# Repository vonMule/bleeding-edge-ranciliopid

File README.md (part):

# PERFECT COFFEE PID 
(former bleeding edge ranciliopid)

## Do it yourself, open-source PID for your espresso machine  

Version 3.2.5

## Support / Contact
You can chat with us directly using our [discord server](https://discord.gg/VA5ZeacFdw).

## Videos

<details>
  <summary>Click for more videos!</summary>

| Description             |  Video |
:-----------------------------------------------:|:---------------------------------------------:
ESP32 Functions with full Softwarecontrol | 
Cleaning Mode | 
Waterlevel Sensor | 
Two cups of a double cappuccino with the new Steamfunction | 
</details>

&nbsp;

## Most important features compared to the rancilio-pid software:
1. New PID Controller "Multi-state PID with steadyPower (Bias)"
   - Target-Temperature for brewing and steaming (!) is automatically controlled by PID.
   - Auto-Tuning of all PID settings. No knowledge or special tunings required.
   - Distinct PID settings dependend on the current "state" of the machine. 
   - Most of the settings are either static or semi-automatically tuned, which does not require an PHD (German: Diplom) to understand.
   - Currently 5 states are implemented:
     - Coldstart (machine is cold)
     - Coldstart stabilisation (directly after coldstart)
     - Inner Zone (temperature near setPoint)
     - Outer Zone (temperature outside of "inner zone")
     - Brewing
     - Steaming (!)
   - steadyPower is introduced which compensates the constant temperature loss due to environment
   - steadyPowerOffset is introduced which compensates the increased temperature loss when the machine (brew head etc.) is still very cold.
   - PidController offers feature like I-value filtering, special handling of setPoint crossings and more (hard-coded)
   - PID Controller is now integral part of the software and not an external library.
1. FULL ESP32 (and of cause esp8266) support in bleeding-edge main-branch.
1. Support of three hardware modifications which matches you requirements and offers the best flexibility.
   - PidOnly: This is the most basic modifcations in which only the heater is controlled by the esp.
   - Standard: In this modifcations in addition to the heater, "brewing" is also controlled by the esp which enables pre-infusion (by cutting the "hardware-button switched" power to the valve and the pump on demand).
   - FullControl: (ESP32 only) All functionality is directly controlled by the esp. This allows full customization and implementation of any feature. Also all functionality can therefore remotely be activated/deactivated. The ESP32 can run 24/7 if required.
1. Freely choose if you want the software to use WIFI, BLYNK and/or MQTT. Everythink can be enabled/disabled and still have a flawlessly working PID controller.
1. Additionally if you want to to depend on a remotely running service (eg. blynk server on raspi), you can activate a MQTT-Server on the arduino itself!
1. By using the actionController you can freely configure the system to trigger custom ACTIONS (=functions) when a GPIO port is triggered (eg by a switch) or when commands are received over network (mqtt/blynk).
   - fully dynamic mapping of any(!) available analog/digital gpio port to trigger following custom ACTIONS:
     - BREWING   := start brewing
     - STEAMING  := automatically manages heat up machine for steaming
     - HOTWATER  := start pouring hotwater
     - HEATER    := activate heater (not yet)
     - PUMP      := activate pump (not yet)
     - VALVE     := activate Valve  (not yet)
     - CLEANING  := activate cleaning mode
     - SLEEPING  := activate sleeping mode
     - MENU      := activate menu
     - MENU_INC  := increase value shown in menu
     - MENU_DEC  := decrease value shown in menu
   - while also supporting the switch types: toggles (eg switches) and triggers (eg push buttons)
   - added MQTT support to control ACTIONS using topics ../actions/<ACTION> with supported payloads of 0|1|-1 (off|on|switch)
     Example: "custom/Küche.Rancilio2/actions/STEAMING"
   - added Blynk support to control ACTIONS using virtual pins
1. MultiToggle triggers any ACTION based on multiple simultaneous hardware-button states (eg. if hotwater+steaming button is pressed then start the action CLEANING). MultiToggle can trigger up to six ACTIONS just by using the three rancilio's hardware-switches and therefore reduces the need for external control (mqtt, blynk, resistor-circuit, ..).
1. GpioAction: When actions are activated, specific GPIOs can be triggered also. This can be used eg. to light up LEDs in Rancilio's custom modified hardware-switches.
1. "Brew Profiles" can be used to easily set optimum brew settings for different beans.
1. Scale support to optionally brew by weight (in addition to by time).
1. Offline Modus is fixed and enhanced. If userConfig.h's FORCE_OFFLINE is enabled, then PID fully is working without networking. Ideal in situations when there is no connectivity or you dont want to rely on it.
1. Huge performance tunings and improvements under the hood which stabilizes the system (eg in situations of bad WIFI, hardware issues,..).
1. MQTT support to integrate machine in smart-home solutions and to easier extract details for graphing/alerting.
1. ACTION "SLEEPING" can be used to shutdown heater and turn the display off either after a period on user inactivity (default 120min) or by user request. Any user activity (controlActions, Hardware-Buttons, MQTT Actions, brew Detection,..) will wake up the maschine.
1. Added RemoteDebug over telnet so that we dont need USB to debug/tune pid anymore (https://github.com/JoaoLopesF/RemoteDebug). While using OTA updates you can remotely debug and update the software!
1. "Brew Ready" Detection implemented, which detects when the temperature has stabilized at setPoint. It can send an
   MQTT event or have hardware pin 15 triggered (which can be used to turn a LED on).
1. All heater power relevant settings are now set and given in percent (and not absolute output) and therefore better to understand
1. Support for customizable item collections to beautify display output (thanks to helge!)
1. Safetly toogle added to shutdown heater on sensor malfunction (TEMPSENSORRECOVERY)
1. Many useful functions to be used internally getAverageTemperature(), pastTemperatureChange() + updateTemperatureHistory())

## ATTENTION:
- This software is tested thoroughly with the pid-only hardware solution on Silvia 5e, and with a permanently run full-hardware solution on an 10 year old Silvia. Also a 10 year old Gaggia Classic is tested successfully. I am grateful for any further feedback. 
- Please monitor our machine's temperature closely the first few run times. The muti-state pid controller should never lead to temperatures greater than 5 degress above setpoint!

## Sample data log
- You can use the mqtt interface to export live data for monitoring purposes as can be seen in this [Grafana Dashboard](https://snapshot.raintank.io/dashboard/snapshot/lYe7XigrehSfVsvAWYifEwd2d5hNC0dl).

## Instructions on how to migrate from official rancilio to bleeding-edge
Installation is as explained on http://rancilio-pid.de/ but with following adapations:
1. Make screenshots of the official "Blynk App Dashboard" so that you can revert anytime.
1. Copy file userConfig.h.SAMPLE to userConfig.h and edit this file accordingly.
   - I propose to set MQTT_ENABLE=2 instead of blynk. But it is up to you.
     ```
     #define MQTT_ENABLE 2
     ```
1. Copy contents of folder ranciliopid\arduino-libs to your arduino sketchbook location (normally C:\Users\YOUR_NAME\Documents\Arduino)
   - Important: Open arduino IDE and configure the setting Tools->"lwip Variant" -> "1.4 High Bandwidth"
1. Flash and enjoy your espresso.
1. No tuning should be required normally. If you want/need to then use the method described below.

## Instructions on how to update to the latest version of bleeding-edge
1. Just overwrite all existing files with a newly released version.
2. Open your userConfig.h file, which had not been overwritten in previous step, and manually check (line by line!) that all updates to the new file userConfig.h.SAMPLE are reflected in your own userConfig.h. 
3. Compile, upload and enjoy!

## Remote Control APIs
- MQTT
  - Instructions can be found at https://github.com/medlor/bleeding-edge-ranciliopid/wiki/MQTT-Setup
- Blynk
  - Instructions can be found at https://github.com/medlor/bleeding-edge-ranciliopid/wiki/Blynk-Setup

## Tunings instructions
- Instructions can be found at https://github.com/medlor/bleeding-edge-ranciliopid/wiki/PID-Tuning

## Debugging Howto
- Instructions can be found at https://github.com/medlor/bleeding-edge-ranciliopid/wiki/Debugging-Howto

## How to use a simple LED as brewReady signal
- Instructions can be found at https://github.com/medlor/bleeding-edge-ranciliopid/wiki/How-to-use-a-simple-LED-as-brewReady-signal

## Instructions on how to create new icon collections
- Instructions can be found at https://github.com/medlor/bleeding-edge-ranciliopid/wiki/Instructions-on-how-to-create-new-icon-collections

## Changelog
- 3.2.5:
  - Feature: Add local(!) MQTT Broker support on ESP32. Finally you can have MQTT without an external running broker. Many thanks to bviecelli!
  - Fix: Upgrade to Expressif v6.5.0
  - Some bugfixes on the new broker integration.
- 3.2.4:
  - Many more refactorings by aschoelzhorn. Thanks again!
    - Seperated wifi, temperature and other code to dedicated files. 
    - Introduces rancilio-enums.h file and replaced some defines with enum classes.
    - Reorganized OTA (init and handle), OTA code still in "rancilio-pid.ino" because of timer stuff.
    - Separated declaration and implementation in some header/code files.
  - Part cleanup of includes.
  - Some bugfixes and refactorings by Tobias.
- 3.2.3:
  - Feature: On OTA Update show special logo and progress. Thanks aschoelzhorn!
  - Feature: Enable bigger status icons when ENABLE_BIG_STATUS_ICONS is set to 1 (default 0). Many thanks aschoelzhorn!
  - Refactor: Code refactorings. Many thanks aschoelzhorn!
  - Fix: Wifi stability improvements.
    - Disable WiFi Power Safe.
    - Reduce WiFi retry wait times.
    - WiFi instability by adding housekeeping times.
  - Changed minimum retry timer when mqtt/blynk disconnects happen from 160s to 60s.
  - Fix: Changing MQTT settings while machine being offline is being honored again.
  - Fix: Blynk working again with latest version.
  - Added Blynk state caching.
  - Fix: Some "include" issues when arduinoIDE is used. Thanks Helge!
  - Fix: Support for Expressif v5.3.
  - Performance improvements. 
  - Removed legacy grafana.
- 3.2.2:
  - Refactor: Moved blynk code into own files. Thanks aschoelzhorn!
  - Refactor: Add a temperature sensor mock. Thanks aschoelzhorn!
  - Refactor: Replace state magic numbers with meaningful names. Thanks aschoelzhorn!
  - Fix: Schematic_bleeding_edge_full_control_pcb_layout_v0.7.png, was wrong at one place.
- 3.2.1:
  - Feature: Add support for SH1106 in SPI mode. Thanks piontec!
  - Feature: Add support for custom display pins (see DISPLAY_I2C_SCL, DISPLAY_I2C_SDA). Thanks piontec!
  - Feature: Distinguish triggertype for 3way-valve and pump. Thanks piontec!
  - userConfig.h Changes:
    - Added VALVE_TRIGGERTYPE, PUMP_TRIGGERTYPE (default HIGH. Previously called TRIGGERTYPE).
    - RENAMED pinRelayVentil to pinRelayValve.
    - RENAMED pinRelayPumpe to pinRelayPump.
    - Added DISPLAY_I2C_SCL, DISPLAY_I2C_SDA (default 255).
  - Fix: SSD1306 support should also work again. Thanks piontec!
  - Added IoTMQTTPanel-perfect_coffee_pid_v3.2.0_v1.json to support the "new" scale settings.
  - Fix: Changed BREWTIME_END_DETECTION to type "bool" to improve handling of improper configuration.
  - Upgrade ZACWire to v2.0.0. Thanks Adrian/lebuni.
  - Refactored GpioCheck accordingly.
  - Updated ESP boardmanager and library dependencies to latest official version:
    - Platformio:
      - esp32: Upgrade espressif32 from v3 to v5
      - FastLED to v3.5.0
      - esp8266: Upgrade espressif8266 from v2 to v4
      - esp8266: Update to latest uMQTTBroker
    - ArduinoIDE:
      - Upgrade Boardmanager from 
        - ESP32:v1.0.6 to v2.0.4 
        - ESP8266:v2.7.4 to 3.0.2
      - Important: Update all manually installed libs like RemoteDebug and ZACWire (see Wiki)!
- 3.2.0:
  - NEW FEATURE (ESP32 & ONLYPID=0): Add *SCALE* functionality for brewing based on a PR by [Hoondie](https://github.com/avolmensky) (Many thanks Hoondie!).
    - Rewrite of brew() function to supports stopping brewing by time or weight (see userConfig.h BREWTIME_END_DETECTION):    
    - Setup guide in [Wiki](https://github.com/medlor/bleeding-edge-ranciliopid/wiki/Scale-Setup)
      - 3D printer models:
        - [3D Scale Case made by Hoondie](https://www.thingiverse.com/thing:5226789) (Many thanks Hoondie!).
        - [PerfectCoffeePid Scale Case](https://github.com/medlor/bleeding-edge-ranciliopid/tree/master/3d-models/PerfectCoffeePid-Scale). 
    - Display shows actual weight while brewing and additionally brewStatistics/flowRate a couple of seconds after brew (all themes are supported).
    - Automatic tuning of target-weight offset to adapt to dipping effects after brew ends.
  - Refactoring und noticeable further features:
    - Implemented manual calibration feature:
      - Howto: 
        - Set ENABLE_CALIBRATION_MODE=1, start machine without any weight on the scale, 
          after around 20s put a known weight (which is set in SCALE_SENSOR_CALIBRATION_WEIGHT) on the scale.
          The LOG will show the calculated SCALE_SENSOR_CALIBRATION_FACTOR which has to be added to the userConfig.h .
    - Send brewStatistics to display, mqtt events and LOG: "Brew statistics: 37.36g in 29.78s (1.25g/s) with profile 1".
      - FlowRate also included in output.
      - Display shows brewStatistics after brew for a couple of seconds.
    - Use powerOff and powerUp to save energy and to reduce interrupt conflicts. HX711 is only enabled when brew is running. 
    - 3rd party library for the HX711_ADC by Olav Kallhovd (https://github.com/olkal/HX711_ADC) adapted to our needs (Many thanks Olav!):
      - [custom async implementation](https://github.com/medlor/HX711_ADC) while using ISR to ...
        - reduce processing delays
        - reduce competing interrupts between TSIC, display and scale
        - no TSIC errors!
    - Auto-tare weight (async; without delay) at start of brew.
    - After brew is finished weight is measured for an additional 2 seconds (to include drops after the pump has stopped).
    - If HX711 cannot be initialized on start of brew, fallback to time-based brewing.
    - New scale settings are now tied to "Profiles":
      - Set following settings in userConfig.h / MQTT / "CONTROLS_CONFIG" / Blynk (V64 := activeBrewTimeEndDetection , V65 := activeScaleSensorWeightSetPoint):
        - BREWTIME_END_DETECTIONX: if 0, stop by time else stop by weight 
        - SCALE_SENSOR_WEIGHT_SETPOINTX = weight when to stop brewing
    - Custom scaleConfigOverwrite.h
    - ArduinoIDE: Added library/HX711_ADC_fix which has to be manually copied to your arduino library path. (see wiki)
    - ArduinoIDE: Successfully compiles (in addition to Platformio).
  - ArduinoIDE: "library/RemoteDebug" minor compile fix.
  - ArduinoIDE: Add check to force esp32 board version 1.0.6.
  - brew() is only called at most every 1ms.
  - Fix: If you have an analog toggle configured for BREWING and dont turn it off before power-off, 
      then brewing will no longer automatically start on power-on.
  - userConfig.h Changes:
    - BREWTIMER_MODE renamed to BREWTIME_TIMER
    - Many new defines called SCALE_SENSOR_*
    - Added BREWTIME_END_DETECTIONX
    - Added SCALE_SENSOR_WEIGHT_SETPOINTX.
    - Added SCALE_SENSOR_CALIBRATION_WEIGHT, SCALE_SENSOR_CALIBRATION_FACTOR
    - Updated circuit-diagrams to add HX711.
- 3.1.1:
  - Fix: Coldstart working again.
- 3.1.0:
  - NEW FEATURE: Add support for up to 3 "*Profiles*", which can be used to quickly switch between different brew settings (eg. when different beans are used).
    - An individual profile comprises of following settings:
      - Brew Temperature / setPoint
      - Brew Time 
      - Preinfusion time and pause
      - Coldstart Temperature / startTemp
    - Profiles can be selected by any means, eg mqtt/blynk/menu/.. . The variable for this is "profile".
    - The selected profile is also shown on the display, see new setting ENABLE_PROFILE_STATUS.
    - ATTENTION: Following variable names has changed and therefore any mqtt dashboards and tools have to be adapted (eg IotMQTT/Grafana/nodered):
      - setPoint -> activeSetPoint
      - brewtime -> activeBrewTime
      - starttemp -> activeStartTemp
      - preinfusion -> activePreinfusion
      - preinfusionpause -> activePreinfusionPause
      - Hint: Changing the value of any of variables (eg using mqtt/blynk) will update the respective setting of the currently activated profile.
    - Blynk:
      - Added new virtual Pin V3 for "profile", which can be any number between 1 and 3.
      - Added [Blynk Showcase](https://github.com/medlor/bleeding-edge-ranciliopid/tree/master/blynk/blynk-showcase_v3.1.0.mp4).
  - NEW FEATURE: Initial support for MENU which can be used to control settings using the display-case with buttons:
    - Action "MENU" added.
    - Actions TEMP_INC and TEMP_DEC renamed to MENU_INC and MENU_DEC respectively.
    - Added new userConfig.h setting MENU_CONFIG which is used to configure menu settings.
    - Following menu operations are supported (can be extended on request):
      - SETPOINT, SETPOINTSTEAM, BREWTIME, PREINFUSION, PREINFUSION_PAUSE, PID_ON
  - NEW FEATURE: The calculation of the "total brew time" can be adjusted with the userConfig.h setting BREWTIMER_MODE.
     - 0: (default) brewtime-countdown is equal BREWTIMEX. 
     - 1: brewtime-countdown is BREWTIMEX + PREINFUSIONX + PREINFUSION_PAUSEX
  - userConfig.h Changes:
    - Added:
      - ENABLE_PROFILE_STATUS
      - Renamed SETPOINT to SETPOINT1
      - Renamed BREWTIME to SETPOINT1
      - Renamed PREINFUSION to PREINFUSION1
      - Renamed PREINFUSION_PAUSE to PREINFUSION_PAUSE1
      - TEMPSENSOR (default=2)
      - SETPOINT2, SETPOINT3
      - STARTTEMP2, STARTTEMP3
      - PREINFUSION2, PREINFUSION3
      - PREINFUSION_PAUSE2, PREINFUSION_PAUSE3
      - BREWTIMER_MODE
  - Support for Thermistor K-type with MAX6675 (Thanks to aschoelzhorn for the PR and TeraK, sailhobie for support).
    - TSIC3xx is still strongly recommended to use!
  - Updated IoTMQTT Dashboard [IoTMQTTPanel-perfect_coffee_pid_v3.1.0_v1.json](https://github.com/medlor/bleeding-edge-ranciliopid/tree/master/IoTMQTTPanel/IoTMQTTPanel-perfect_coffee_pid_v3.1.0_v1.json) to include Profile and Action support. [Showcase](https://github.com/medlor/bleeding-edge-ranciliopid/tree/master/IoTMQTTPanel/IoTMQTT-showcase_v3.1.0.mp4).
  - Refactor and fix eeprom stuff.
  - Refactor all variables from double to float.
  - Make blynk optional on compilation.
  - Removed burst feature.
  - Fixes:
    - Fix blynk "heater output" not being shown.
    - Fix float compare function.  
- 3.0.0:
  - Project is getting renamed to "Perfect Coffee PID".
  - Improve temperature readings to reduce undesireable actions of the PID controller:
    - Detect outliers near setpoint and fix them automatically.
    - Read temperature every 100ms (previous 1s) and save it to TemperatureHistory for later use.
    - Implement average calculations on all temperature functions to stabilize temp readings.
    - Temporary use custom ZACwire library, which offer:
      - bitwindow auto-tuning right from the start.
      - directMode to improve outlier detection and flapping temperature in seldom cases (esp32).
      - Important: You have to [manually install](https://github.com/medlor/bleeding-edge-ranciliopid/wiki/How-to-compile-on-Arduino-and--Platformio) library/ZACwire_for_TSic (only if you are using Arduino IDE).
  - Add full support for platformio, code cleanup and fix compile warnings.
    - Force espressif8266 to Version 2 (until external libs are adapted)
  - Arduino IDE: Remove some libaries which from now on have to be installed manually, see [Wiki](https://github.com/medlor/bleeding-edge-ranciliopid/wiki/How-to-compile-on-Arduino-Platformio).
  - Performance improvement: 
    - controlActions are now using interrupts with an optional debounce feature (instead of polling each gpio).
  - Update ESP32 schematic to reflect recommendation to use 5v (instead of 3.3v) for the TSIC.
  - Fix: 
    - DISPLAY_TEXT_STATE is working on exp8266.
    - controllerActions: Improve debouncing of analog(ADC) and digital buttons/switches.
    - Improve steaming cycle-times.
  - Remove support for DS19B20 temperature sensors.
  - Improvements in error logging.
  - UserConfig Changes:
    - Breaking Change:
      - renamed DISPLAY to DISPLAY_HARDWARE
    - Removed:
      - TEMPSENSOR
    - Added:
      - DEBOUNCE_ANALOG_GPIO / DEBOUNCE_DIGITAL_GPIO
    - Changes:
      - recommended defaults
- 2.8.0:
  - Feature: Add support to detect low water using a VL53L0X Time of Flight distance sensor. see [Howto](https://github.com/medlor/bleeding-edge-ranciliopid/wiki/Water-level-measurement-using-VL53L0X-(Time-of-Flight-distance-sensor))
  - Helge supplied a 3d printing model for rancilio silvia's water tank lid which can be used with the VL53L0X sensor. (thanks Helge!)
  - Update ZACWire to v1.3.2. (Thanks Adrian)
  - UserConfig change: 
    - Renamed DEBUG_FORCE_GPIO_CHECK to ENABLE_CALIBRATION_MODE.
  - Fix: Show general logo when MASCHINE_TYPE is set to unknown.
- 2.7.1:
  - Added PR for automatic cleaning mode (Thanks to urbantrout/Harald).
    - Adaptions:
      - New cleaning icon: ["washing hand"](https://thenounproject.com/matfine/collection/cleaning-icon/?i=2749704) by [Mat fine](https://thenounproject.com/matfine) from [the Noun Project](https://thenounproject.com/matfine/collection/cleaning-icon/?i=2749704) licensed under [CC BY 3.0](https://creativecommons.org/licenses/by/3.0/legalcode)
      - New Blynk VPins (read-only/pull) defined: see [Blynk-Setup](https://github.com/medlor/bleeding-edge-ranciliopid/wiki/Blynk-Setup)
      - New userConfig Settings: 
        - CLEANING_CYCLES, CLEANING_INTERVAL, CLEANING_PAUSE.
        - Set CLEANING_ENABLE_AUTOMATIC=1 to use automatic cleaning program instead of manual modus.
  - Feature: (Silvia5E): ENABLE_POWER_OFF_COUNTDOWN timer (in minutes) is available via mqtt("powerOffTimer")/blynk(V45).
  - Blynk is fully supporting actionController. Therefore any action can be called via blynk. (see [Blynk-Setup](https://github.com/medlor/bleeding-edge-ranciliopid/wiki/Blynk-Setup))
  - Added new icon-collection "static" which just shows a non-moving logo.
  - Added userConfig DISPLAY_TEXT_STATE which outputs few status information (Please wait, Ready, Turned off, Cleaning, ..) in the display (supported by all icon-collections).
    - Text is not displayed when screensaver is running.
  - Fix: Waking up after SLEEPING action re-enables cold-start autotuning.
  - Fix: Blynk sometimes crashes when controlActions are changed.
  - Fix: SLEEPING action will turn off display even if ENABLE_SCREEN_SAVER=0.
  - Fix: DISPLAY_TEXT_STATE is not shown during BREWING.
  - Update ZACwire-Library to v1.3.1. and 1.3.0 (beta). (Thanks again Adrian :-) )
- 2.7.0:
  - Feature: FULLY SUPPORT ESP32 with CPU pinning for improved performance.
    - Unfortuately there is no mqtt-server broker library available for ESP32. (MQTT_ENABLE must not be 2 or disabled on ESP32)
    - Display function is pinned to secondary cpu to further improve performance. No more tearing on screen refresh.
  - [ZACwire-Library](https://github.com/lebuni/ZACwire-Library) upgrade to stable release v1.3.0 which supports ESP32 and pinning to secondary cpu. Thanks Adrian!
  - Feature: "FULL CONTROL" hardware modification is fully supported (in addition to the previous "PidOnly" and "standard" modification)!
    - FullControl have all(!) functionality directly controlled by the esp (eg. without the need to manually switch any buttons).
    - Instead of having the hardware-switches control brew/hotwater/steaming and have the esp just "cut" the wire, the FullControl modification detects button presses directly and translates them to any custom functionality (using ControlActions, MultiToggle and optionally GpioActions). This allows maximum flexibility.
  - Feature: The "MultiToggle" feature triggers any ControlAction based on multiple simultaneous hardware-button states (eg. if hotwater+steaming button is pressed then start the action cleaning).
    - This allows to use a total of six ControlActions just by using the three rancilio's hardware-switches and reduces the need for external control (mqtt, blynk, resistor-circuit, ..).
    - New UserConfig variables: MULTI_TOGGLE_?_ACTION and MULTI_TOGGLE_?_GPIOS.
  - Feature: GpioAction: If actions are activated, specific GPIOs can be triggered also. This can be used eg. to light up LEDs in Rancilio's [custom modified hardware-switches](https://voir.pt/2017/12/30/rancilio-silvia-bezugsschalter-als-softwareschalter-umruesten/).
    - userConfig.h: ENABLE_GPIO_ACTION / pinBrewAction / pinHotwaterAction / pinSteamingAction
    - CLEANING action will turn on the brew/hotwater/steaming gpios to make this state easily visible even when no display is used.
    - During PowerOn GpioActions and HardwareLed are enabled for a couple of seconds.
  - Feature: Added new state "SLEEPING", which shutdowns heater and turns display off either after a period on user inactivity (default 120min) or by user request using the new ControlAction "SLEEPING". Any user activity  (controlActions, Hardware-Buttons, MQTT Actions, brew Detection,..) will wake up the maschine.
    - New userConfig setting: userConfig HEATER_INACTIVITY_TIMER (0 to disable)
  - Feature: (!OnlyPid|Full Control) Added a CLEANING mode which sets pre-infusion pause to 0seconds and disables auto-tuning for as long as mode is active. Use "CLEANING" ControlAction or activate steaming to restore normal operation.
  - Feature: You can now set INPUT/INPUT_PULLDOWN/INPUT_PULLUP in CONTROLS_CONFIG. 
  - Feature: (ENABLE_HARDWARE_LED=2) New settings ENABLE_HARDWARE_LED_RGB_ON/ENABLE_HARDWARE_LED_RGB_OFF to set specific colors.
  - Breaking changes:
    - CONTROLS_CONFIG format changes to support new INPUT/INPUT_PULLDOWN/INPUT_PULLUP settings.
  - CHANGE: (DISPLAY=1) HardwareLed is not turned on when screensaver is running and ENABLE_HARDWARE_LED_OFF_WHEN_SCREENSAVER=1 (even if brew_ready state is reached).
  - Fix: Setting setPointSteam via mqtt did not work but did overwrite aggoTv instead. You should update to this version when using mqtt.
  - Fix: No one-time heater flapping if maschine is waked up from sleep or pidOff.
  - Fix: HardwareLed is only turned on, when temperature > steam_ready_temp AND steaming action is active.
  - Fix: (DISPLAY=1) HardwareLed is not turned on when screensaver is running (even if brew_ready state is reached).
  - Fix: Minor fixes here and there.
  - PubSubClient updated to version 2.8.
  - Update userConfig.h.SAMPLE (Thanks Helge)
  - Fix typos (Thanks urbantrout)
  - (ESP32) Added two new [circuit-diagrams](https://github.com/medlor/bleeding-edge-ranciliopid/tree/master/circuit-diagrams) which show the complete wiring in "full-control" upgrade.
  - Added several 3d models to print:
    - display-case-with-buttons
    - dual-ssr-relay-case
    - pcb-case (eg. to be used for esp32 on a pcb)
  - New images here and there.
  - Quick documentation on how to setup ESP32 can be found in the [wiki](https://github.com/medlor/bleeding-edge-ranciliopid/wiki/ESP32-Setup).
  - Thanks to Tobias for his helpful blog posts at [https://voir.pt](https://voir.pt/2017/12/30/rancilio-silvia-bezugsschalter-als-softwareschalter-umruesten/)
- 2.6.1:
  - Feature: Hardware-Led in addition to simple LEDs also support WS2812b LED (stripes) (MANY THANKS P1Rebo for the PR)
- 2.6.0:
  - Merged PR by finnito which changed/extended: (MANY THANKS FINNITO)
    - Added support for ECM espresso machine including logo.
    - Added/Extended support for special functions (steam, hotwater, brew).
    - Added custom steam functionality.
    - Extended initial support to call special functions based on Pin A0 (analog levels) which can be used by eg. hardware buttons.
    - Added new state to state machine (6=steam).
  - Refactored/Extended finnito's code to integrate our new "actionController":
    - fully dynamic mapping of any(!) available analog/digital gpio port to custom functions, which are currently:
      - BREWING   := start brewing
      - STEAMING  := automatically manages heat up machine for steaming
      - HOTWATER  := start pouring hotwater
      - HEATER    := activate heater (not yet)
      - PUMP      := activate pump (not yet)
      - VALVE     := activate Valve  (not yet)
      - CLEANING  := activate cleaning mode (not yet)
      - TEMP_INC  := increase setPoint (not yet)
      - TEMP_DEC  := decrease setPoint (not yet)
    - while also supporting the switch types: toggles (eg switches) and triggers (eg push buttons)
    - added MQTT Support to control actions using topics ../actions/<ACTION> with supported payloads of 0|1|-1 (off|on|switch)
      Example: "custom/Küche.Rancilio2/actions/STEAMING"
  - Feature: Set userConfig.h ROTATE_DISPLAY to rotate display 180 degree.
  - Feature: BrewReadyLed (now called HardwareLed) configured with ENABLE_HARDWARE_LED also lights up when temperature>steamTemp or >STEAM_READY_TEMP.
  - Feature: OnlyPid=0: Disable pre-infusion and pause if userConfig settings are set to 0.
  - Feature: OnlyPid=1: BrewDetection can also be triggered by hardware using actionControl "BREWING".
  - Feature: New userConfig setting SETPOINT_STEAM is also setable via [mqtt](https://github.com/medlor/bleeding-edge-ranciliopid/wiki/MQTT-Setup)/[blynk](https://github.com/medlor/bleeding-edge-ranciliopid/wiki/Blynk-Setup).
  - Feature: hardwareLed will glow for a few seconds when the machine starts up. This helps determine a not-starting node.
  - Feature: Additional safe-guard to temporary disable heater if temperature is 10 degree above active setPoint.
  - Important FIX: mqtt interface for STEADYPOWER_OFFSET_TIME working again. This setting is currenly wrongly set and need to be re-set for auto-tuning to work!
  - Fix: EMERGENCY_TEMP setting disables pid when temperature is > and re-enables when < setPoint. Please check your setting to be reasonable high (eg. Rancilio 135 degree). Should at least be higher than SETPOINT_STEAM.
  - Feature/Fix: New setting STEAM_READY_TEMP to show our special steaming-icon only when temperature is above.
    - There is support for special "in-steaming-state" icons, but I am in no mood to paint them yet. Feel free. 
  - BREWDETECTION_POWER is now in active right after a brew is detected and not when temp <1.5degree below setpoint.
  - Attention: Major userConfig adaptions. Create a backup!
    - BREAKING CHANGE: 
      - OnlyPid=1: Software based brewDetection has to set with "2" (and not "1"!!) in userConfig BREWDETECTION.
    - Added:
      - SETPOINT_STEAM
      - STEAM_READY_TEMP
      - CONTROLS_CONFIG
      - DEBUG_FORCE_GPIO_CHECK
      - ROTATE_DISPLAY
    - Removed:
      - pinBrewButton (replaced by CONTROLS_CONFIG)
      - EMERGENCY_ICON
      - OTAHOST (use HOSTNAME instead)
      - ENABLE_USER_MENU
    - Changed:
      - Default of userConfig EMERGENCY_TEMP from 125 to 128.
      - Default of userConfig TEMPSENSORRECOVERY from 1 to 0.
  - Sample Config for IoTMQTTPanel: IoTMQTTPanel-rancilio_v2.6.0_v1.json
  - Update ZACwire-Library to v1.1.3.
- 2.4.2 master:
  - Bugfix: Revert changes in regard to compiler warnings added in 2.4.1.
  - Bugfix (MQTT_ENABLE=1): Auto-Tuning settings are persisted across restarts.
  - Bugfix: steadyPowerOffsetTime is configurable via mqtt.
  - Bugfix: aggoTn is now correctly published via mqtt.
  - Added new circuit-diagrams (Thanks Tempcookies + Helge).
  - MQTT code refactorings.
- 2.4.1 master:
  - It fixes some compiler errors and warnings I was seeing on my system. (Thanks nils-werner)
  - It contains a small platformio.ini file for Platformio support. (Thanks nils-werner)
- 2.4.0 master:
  - Special winter theme added. Activate with ICON_COLLECTION=2 in userConfig.h.
  - Added support for a customizable screen-saver (#define ENABLE_SCREEN_SAVER)
  - Overwrite Version info at boot time via OVERWRITE_VERSION_DISPLAY_TEXT in userConfig.h.
  - Added power-off countdown to hint the user when the machine is going to shutdown (ENABLE_POWER_OFF_COUNTDOWN) (Silvia 5E)
  - Power-off countdown starts 5min before shutdown.
  - Bugfix: Fix brew detection (OnlyPid)
  - Bugfix: End of BrewTimer correctly displayed (OnlyPid)
  - Bugfix: No power-off countdown when brewing.
  - Move display stuff into separate files
  - alpha code: Intitial support for an user-menu (ENABLE_USER_MENU/pinBrewButton)
  - alpha code: Initial infos about how to add a case with hardware-buttons to control basic settings directly at machine.
- 2.3.0 master:
  - PID is completely auto-tuned and should work flawlessly after a few starts. No need to configure PID any longer. 
  - Bleeding-Edge settings can be configured remotely without requiring a running service (blynk, mqtt-server) running in your network or internet. (No extra raspi required)
    You can now freely choose which service you want to use:
    1. Standalone without any network connectivity
    2. MQTT Server (runs on bleeding-edge arduino) to not depend on a remotely running service
    3. MQTT Client to connect to an mqtt-services (eg used by smart-home software)
  - MQTT fully implemented so you can publish and subscribe to configure settings and monitor states.
  - THANKS: Added Adrian's library to efficiently read TSIC values (https://github.com/lebuni/ZACwire-Library)
  - ATTENTION: New default values in userConfig.h. 
    - It is recommended to intially use default values for STEADYPOWER, STEADYPOWER_OFFSET_TIME, STEADYPOWER_OFFSET, STARTTEMP, BREWDETECTION_POWER, BREWDETECTION_SENSITIVITY. Additionally BREWTIME is from now on also used in ONLYPID=1.
    - GPIO Pin Mapping moved to userConfig.h.
  - ATTENTION: Installation process changed. Libs must be installed as described in "Instructions on how to migrate from official rancilio to bleeding-edge 
    - Copy contents of folder ranciliopid\arduino-libs to your arduino sketchbook location (normally C:\Users\YOUR_NAME\Documents\Arduino)
  - Improve PID:
    - Auto-tuning for starttemp is implemented. No need to adapt the STARTTEMP accordingly when SETPOINT is modified
    - steadyPowerOffset is gradually decreased over time to better compensate the warm up of machine.
    - PID monitors and tunes steadyPowerOffset.
    - One time PID manipulation logic added.
    - PID's I parameter filter is reduced in certain situations more strictly.
  - BrewDetection optimized:
    - (ONLYPID=1) ATTENTION: The BREWTIME setting defines the time-frame of your "normal" brew (in seconds). 
       When a brew is detected, the brew_timer starts and runs until BREWTIME is reached. During that time
       the heater is heating with BREWDETECTION_POWER.
    - BREWDETECTION_POWER behaviour changed: 
      (ONLY_PID=0) The power is applied to heater during the complete brew process. 
      (ONLY_PID=1) The power is applied until the brew_timer is larger than BREWTIME or the current temperature is 1.5 Celcius below setpoint.
    - (ONLYPID=1) BREWDETECTION_WAIT setting added: After a brew is started the software based BrewDetection is disabled for this number of seconds to prevent the detection of another brew when flushing water.
    - (ONLYPID=1) Software BrewDetection estimates the starttime of a brew, so that the brew counter in display is correct. 
  - Debug Logs Improvements:
    - Add logs for brewReadyStatistic
    - When connecting by telnet/blynk the hardware- and software configuration is printed
  - Documentation Updates:
    - Enabled wiki at https://github.com/medlor/bleeding-edge-ranciliopid/wiki/
      - eg. Howto "Setup MQTT": https://github.com/medlor/bleeding-edge-ranciliopid/wiki/MQTT-Setup
    - Added link to sample daily Grafana dashboard.
  - Fix: userConfig.h: AUTH renamed to BLYNKAUTH
  - Fix: No starttemp tuning when when machine is already warm.
  - Fix: burstPower working again.
  - Fix: If PID is manually disabled, heater utilization is correctly reported as 0%.
  - Fix: Heater overextending handling working as intended.
  - Fix: Potential crash when toogling pid on/off
  - Fix: Save pidON in eeprom.
  - MQTT_ENABLE=1: Configuration retained in mqtt topics are now used on startup.
  - Code cleanup and refactorings
  - Trigger brewReady when temperature is stable for 60sec (prev: 40s).
- 2.2.0_master:
  - Display functionality improved:
    - Replaced display lib Adafruit_SSD1306.h with U8G2. Direct support for SH1106_128X64 and SSD1306_128X64 via userConfig.
    - Completly new display widgets which show informations according to active PID state.
    - Support for icon collections to easily customize/share display widgets. Icon collection "simple" and "smiley" included.
    - Support for simple icon animations.
    - Service Status Icons are displayed if enabled in userConfig.
    - New DEFINES in userConfig.h. Update your config.
  - Improvement: Blynk On/Off button re-inits PID state similar to when machine power is turned on.
  - Fix: If DISABLE_SERVICES_ON_STARTUP_ERRORS=1 then WIFI reconnect attempts are also prevented.
  - Remove define EMERGENCY_TEXT.
  - Fix: PID State "brewing" is correctly detected when ONLYPID=0. (Thanks Helge)
- 2.1.0_master:
  - Networking:
    - Huge improvements in handling unstable WIFI networks and mqtt/blynk service unavailabilities.
    - You can disable/enable WIFI, MQTT or Blynk in userConfig.h and stil have a flawlessly working PID controller. Blynk is no longer an hard requirement!
    - Offline Modus is fixed and enhanced. If userConfig.h's FORCE_OFFLINE is enabled, then PID fully is working without networking. Ideal in situations when there is no connectivity or you dont want to rely on it.
    - Fix of EEPROM functionality: PID settings are correctly saved in EERPOM and correctly used if there are WIFI issues.
    - Instead of using dynamic IPs (over DHCPd) you have the option to set a static IP.
    - If blynk or mqtt is not working during startup, do not retry the connection periodically (configurable by userconfig.h DISABLE_SERVICES_ON_STARTUP_ERRORS)
  - New PID Variable "BREWDETECTION_POWER" introduced which defines the heater power during brewing.
  - Complete rewrite of "TSIC sensor read" based on the excellent ISR code by Adrian. (Thanks Adrian!)
    - Optimized "TSIC sensor read" to further increase performance.
    - Currently it takes <4ms to collect sensor data instead of the previous 78ms).
    - Fix: "sensor errors" do not occur anymore.
  - Performance/Stability:
    - Some system libs are optimized in performance and stability (src/ folder).
    - Remove all unneeded external libraries which are installed in system's arduino search path.
    - Code Tunings all over the place to increase performance and therefor stability.
    - Overall stability better by honoring critical processes.
  - Debuglogs can also be accessed via browser (see documentation).
  - PID calculations are moved from ISR to loop(). This improves stability even further.
  - Fix: Brew detection optimized.
  - Safetly feature: Done start brewing if the brew-button is switched "on" on startup
  - Fix: After power on, the 5 second wait time until heater starts is removed.
  - Library path adapted to support Arduino under Linux.
- 2.0.3_beta2:
  - Wifi disconnects handled better.
  - Implement blynk reconnect exponential backoff.
  - Set blynk reconnection timeout (3sec).
  - Added debug messages in ciritical paths.
- 2.0.2_master:
  - stable release
  - updated docs
- 2.0.2_beta2:
  - removed 8x8 display support
  - Code cleanup
- 2.0.2_beta1:
  - Major improvements in display related stuff (eg new icons,..) (thanks helge)
  - Restructure folders (thanks helge)
- 2.0.1_beta8:
  - ISR performance optimised when debug is active (spend time reduced from 0.8ms to 0.15ms).
  - Move DEBUGMODE to config.h.
- 2.0.1_beta7:
  - Emergency Logo can be replaced by a nice "milk steam" logo (EMERGENCY_ICON). (Thanks helge for the icon)
  - Regular status display is beautified and adapted to normal users needs. (Thanks helge for the code)
- 2.0.1_beta6:
  - Fix: Reducing "temperature sensor reading" errors.
  - Fix: steadyPowerOffset_Time is now correctly configurable via blynk.
  - Fix: Hardware switch sensitivity ("brewswitch") is increased from 1000 to 700.
  - Improved: mySteadyPower failure detections.
  - Code Cleanup + Refactorings.
- 2.0.1_beta5:
  - RemoteDebug inactivity time requires a version not yet in arduino library manager. Therefore a workaround is document in the meantime.
  - Pre-Infusion variables are now configurable in config.h: PREINFUSION, PREINFUSION_PAUSE, BREWTIME
  - Emergency temperature theshold is now configurable in config.h: EMERGENCY_TEMP
  - BrewDetection sensitivity is now configurable in config.h: BREWDETECTION_SENSITIVITY (renamed from brewboarder)
- 2.0.1_beta4:
  - Limit auto-tuning of steadyPower to reduce overly increased values.
  - Fix bug in brew().bezugsZeit calculation.
  - Renamed outputK to outputI.
  - Explanation of PID log line added.
- 2.0.1_beta3:
  - Pre-Infusion Values are now in seconds (previously milliseconds).  
    !! ATTENTION: Therefore you HAVE to change following values via blynk: brewtime, preinfusion, preinfusionpause !!
  - Reduce overhead of preinfusion functionality by having it run just every 50ms (and not every ms).
  - Add support for custom emergency text in display when temp >120 degree. (see EMERGENCY_TEXT in config.h.SAMPLE)
  - Emergency temperature threshold can now be set by variable emergency_temperature.
  - RemoteDebug inactivity time increased from 10min to 30min.
  - Add missing line-break in brew() debug logging.
- 2.0.1_beta2:
  - Better Installation Guide
  - Fix brew() function
  - Support virtual BrewReady LED in blynk
  - Improve pastChange() in Pid.compute(). (default Kd value has to be doubled)
  - Improve Auto-tuning.
  - Default PID Value Tunings
- 2.0.1_beta:
  - ATTENTION: EEPROM has changed. Therefore you have to connect to blynk at least once, and manually set correct settings in blynk app (see screenshots for default values).
  - New PID Controller "Multi-state PID with steadyPower (Bias)"
  - "Brew Ready" Detection implemented, which detects when the temperature has stabilized at setPoint. It can send an
    MQTT event or have hardware pin 15 triggered (which can be used to turn a LED on).
  - Because deadtime of Silvia5E is around 45seconds PID.compute() runs every 5 seconds (previous 1sec) and reduce header on/off switches by factor 5
  - Temperature polling is also now set to once every second (previous 400ms)
  - Code refactoring/cleanup and fixes of bugs.
  - BurstShot feature added to temporary overwrite PID controls (useful mainly for tests)
  - Added RemoteDebug over telnet so that we dont need USB to debug/tune pid anymore (https://github.com/JoaoLopesF/RemoteDebug)
    - Just "$ telnet rancilio_ip 23"
  - Fix: Recover EmergencyStop when temperature poll in setup() fails
  - EmergencyStop state logging improved
- 1.9.8h_alpha:
  - Feature: Implemented special 3 step cold-start mechanism. See special tuning instructions above.
- 1.9.8g:
  - Improvement: Broken temperature is detected when temp has increased more than >5 degrees (previous 25 degrees) in the last 0.4 seconds.
  - Improvement: Better brewReady detection by waiting for stable temperature within a longer time window (from 6 to 14secs).
  - TemperatureHistory increased from 6 seconds to 30seconds.
- 1.9.8f:
  - Added missing config.h.SAMPLE variables.
  - Added some more mqtt events.
- 1.9.8e:
  - Removed movAvg() due to several issues:
    - This is no moving avg, but something different (but it is working for "stable" temperature curves).
    - readIndex=0 is not used.
    - movingAvg does not compares currentValue with previousValue.
    - Faktor *100 makes no sense (?).
    - initializing methods/firstreading is refactored.
  - movAvg() is replaced by pastTemperatureChange() (+ updateTemperatureHistory())
  - Change order of brew-detection in main loop() to not confuse bPid.compute() due to flapping setTunings()
  - Feature: isBrewReady() to determine if temperature is stable to start brewing
  - Bugfix: Replace abs() with fabs().
- 1.9.8d:
- 1.9.8c:
  - Add more mqtt updates: kp,ki,kd, coldstart
  - Safe-guard: be sure pid internals are cleared when pid is dis/enabled.
- 1.9.8b:
  - Feature: Add support for MQTT.
  - Safeguard: HeaterPreventFlapping must never be > windowSize.
- 1.9.7:
  - Fix: If temperature sensor detects more than 150Celcius then it must be an error.
  - Fix: Typos / explanations.
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
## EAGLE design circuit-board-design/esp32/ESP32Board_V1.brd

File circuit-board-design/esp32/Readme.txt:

ESP32 example PCB made by "Vas#3315" (Attention: this design is not tested)

Vas: I've tested the same design but for Arduino. Sure you can order it from China. 
I've ordered from PCBWay lately, but other guys used JLCPCB successfully. All the 
SMD components are on the top side, so any manufacturer who offers one side SMD 
assembly will work. I've built the BOM for LCSC, it's in the schematics.

Link to easyEDA: https://oshwlab.com/Vas_/esp32board_v1

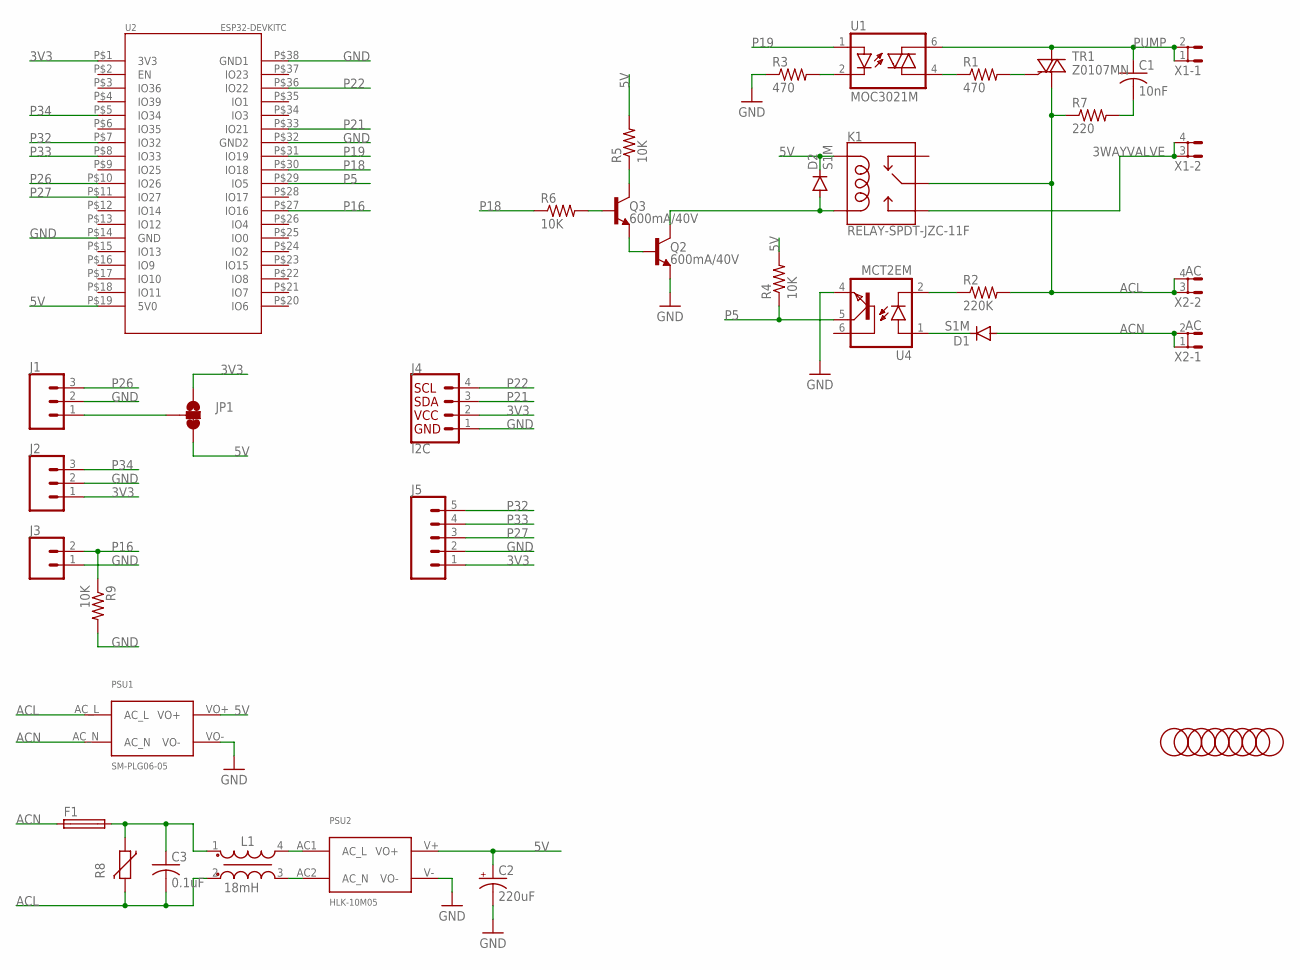
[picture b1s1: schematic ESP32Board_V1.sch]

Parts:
C1: 10nF; C075-032X103
C2: 220uF; E2,5-6
C3: 0.1uF; C150-054X183
D1, D2: S1M; SMA
F1: FUSETE5; TE5
J1, J2: CONN_03JST-PTH; JST-3-PTH
J3: CONN_02JST-PTH-2; JST-2-PTH
J4: I2C; JST04_1MM_VERT
J5: CONN_05JST; JST-5-PTH
JP1: JUMPER-SMT_3_1-NC_TRACE_SILK; SMT-JUMPER_3_1-NC_TRACE_SILK
K1: RELAY-SPDT-JZC-11F; RELAY-JZC
L1: 18mH; WE-TFC_UU9.8V
PSU1: SM-PLG06-05; SM-PLG06
PSU2: HLK-10M05; HLK-10MXX
Q2, Q3: 600mA/40V; SOT23-3
R1, R3: 470; R0603
R2: 220K; R0603
R4, R5, R6, R9: 10K; R0603
R7: 220; R2512
R8: VARISTOR-7,5; R-7,5
TR1: Z0107MN; SOT223
U1: MOC3021M; DIL06
U2: ESP32-DEVKITC
U4: MCT2EM; PDIP6_8P89X6P60_ONS
U$1, U$2, U$3, U$4, U$5, U$6, U$7, U$8: FIDUCIAL; FIDUCIAL_1MM
X1: SH5-2
X2: AC; SH5-2

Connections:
3V3: J2.1, J4.2, J5.1, JP1.1, U2.P$1 (3V3)
3WAYVALVE: K1.3 (NO), X1.3 (1), X1.4 (2)
5V: C2.+, D2.C, JP1.3, K1.5 (COIL1), PSU1.VO+, PSU2.V+ (VO+), R4.2, R5.2, U2.P$19 (5V0)
ACL: C3.2, K1.4 (MAIN), L1.2, PSU1.AC_L, R2.2, R7.1, R8.2, TR1.1 (A1), X2.3 (1), X2.4 (2)
ACN: D1.A, F1.1, PSU1.AC_N, X2.1, X2.2
ACN1: C3.1, F1.2, L1.1, R8.1
GND: C2.-, J1.2, J2.2, J3.1, J4.1, J5.2, PSU1.VO-, PSU2.V- (VO-), Q2.2 (E), R3.1, R9.2, U2.P$14 (GND), U2.P$32 (GND2), U2.P$38 (GND1), U4.4 (EMI)
unnamed: R1.1, U1.4 (A1)
unnamed: R1.2, TR1.3 (G)
unnamed: R3.2, U1.2 (C)
unnamed: C1.2, R7.2
unnamed: R2.1, U4.2 (C)
unnamed: D1.C, U4.1 (A)
unnamed: L1.4, PSU2.AC1 (AC_L)
unnamed: Q2.1 (B), Q3.2 (E)
unnamed: D2.A, K1.1 (COIL2), Q2.3 (C)
unnamed: Q3.3 (C), R5.1
unnamed: Q3.1 (B), R6.2
unnamed: L1.3, PSU2.AC2 (AC_N)
unnamed: J1.1, JP1.2
P5: R4.1, U2.P$29 (IO5), U4.5 (COL)
P16: J3.2, R9.1, U2.P$27 (IO16)
P18: R6.1, U2.P$30 (IO18)
P19: U1.1 (A), U2.P$31 (IO19)
P21: J4.3, U2.P$33 (IO21)
P22: J4.4, U2.P$36 (IO22)
P26: J1.3, U2.P$10 (IO26)
P27: J5.3, U2.P$11 (IO27)
P32: J5.5, U2.P$7 (IO32)
P33: J5.4, U2.P$8 (IO33)
P34: J2.3, U2.P$5 (IO34)
PUMP: C1.1, TR1.2 (A2), TR1.4 (A2), U1.6 (A2), X1.1, X1.2

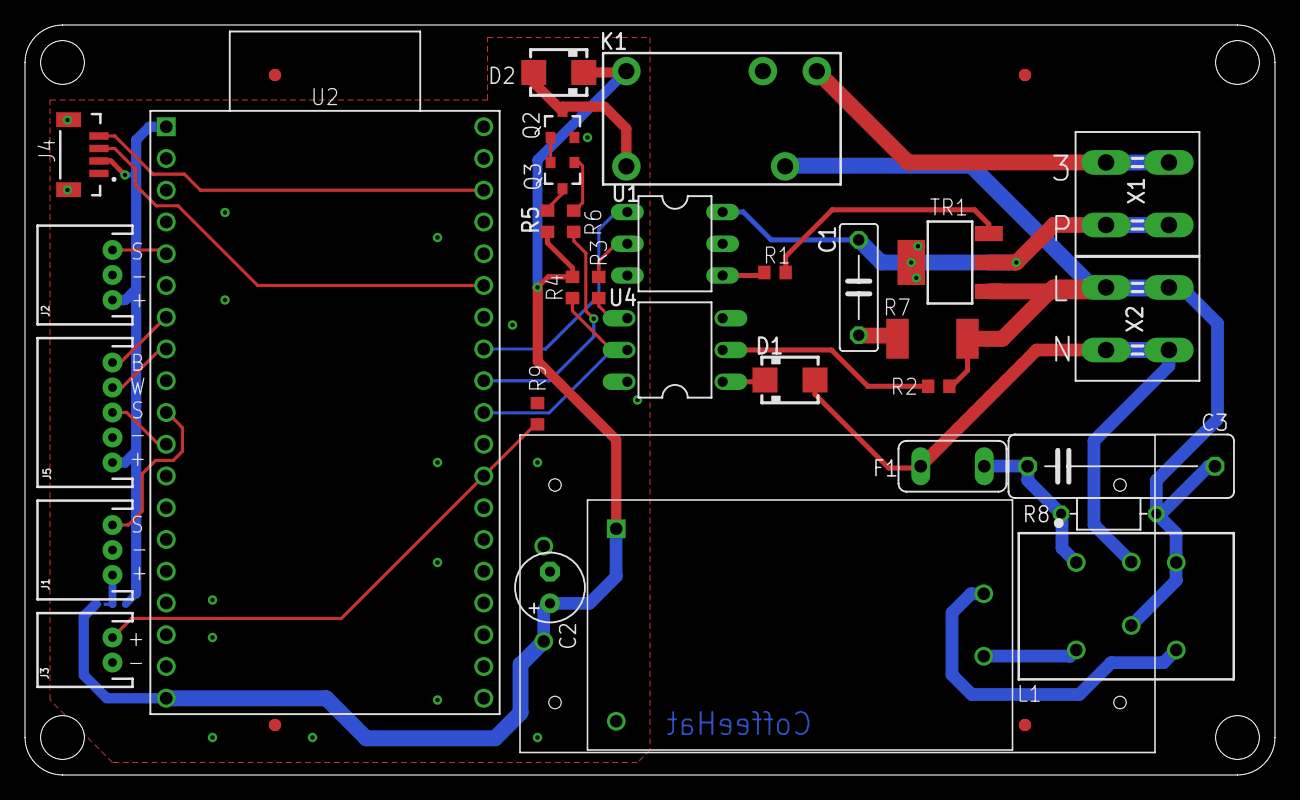
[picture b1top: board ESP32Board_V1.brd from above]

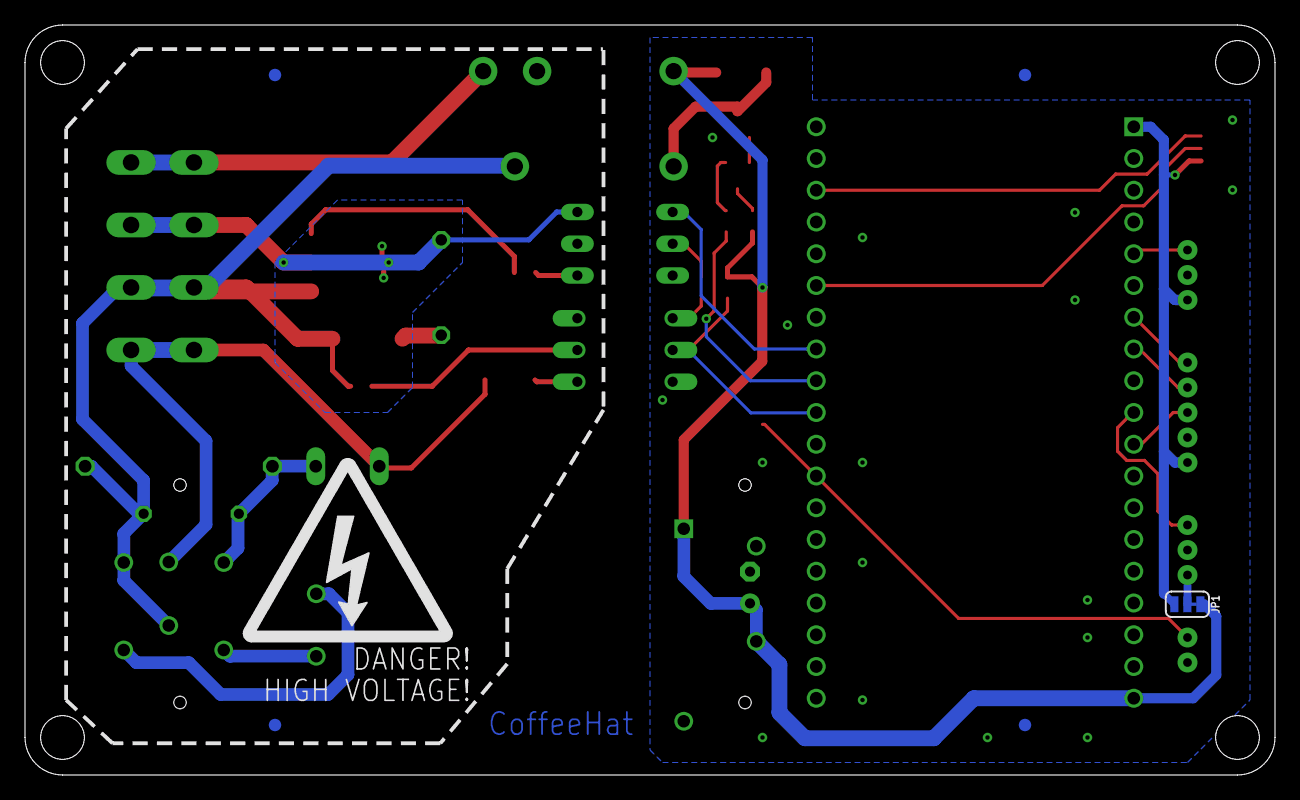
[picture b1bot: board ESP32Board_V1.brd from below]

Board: 2 copper layers, 100.0 x 60.0 mm, 42 parts (6 on the bottom side), 32 nets.

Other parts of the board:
U$9: HV_LOGO_3

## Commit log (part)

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2020-07-13 initial version
2020-07-13 - 2.4.0_beta_0: - Added support for a customizable screen-saver (#define ENABLE_SCREEN_SAVER) - (Silvia 5E) Added power-off countdown to hint the user when the maschine is going to shutdown (ENABLE_P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
2020-07-14 - 2.4.0 beta_1: - Bugfix: Missing defs when MQTT_ENABLE=2
2020-08-01 Fix: (PidOnly) Fix brewing detection.
2020-11-12 - 2.4.0 beta_3: - Bugfix: Fix brew detection (OnlyPid) - alpha code: initial infos about how to add a case with hardware-buttons to control basic settings directly at maschine.
2020-11-16 - 2.4.0 beta_4: - Special winter theme added. Activate with ICON_COLLECTION=2 in userConfig.h.
2020-11-16 - 2.4.0 beta_4: - Special winter theme added. Activate with ICON_COLLECTION=2 in userConfig.h. - Overwrite Version info at boot time via OVERWRITE_VERSION_DISPLAY_TEXT in userConfig.h.
2020-12-20 Fixed compiler errors and warnings
2020-12-20 Platformio config file
2020-12-21 2.5.0 beta: init
2020-12-27 - 2.4.2 beta: - Bugfix (MQTT_ENABLE=1): Auto-Tuning settings not persisted across restarts - Bugfix: steadyPowerOffsetTime is configurable via mqtt. - Bugfix: aggoTn is now correctly published via mq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
2020-12-29 - 2.4.2 beta 3: - Bugfix improvement
2020-12-29 - 2.4.2 beta 4: - Bugfix: Revert compiler warning fix in TSIC. - Bugfix improvement.
2020-12-30 Added ignore for Visual Studio Code Settingsfile
2020-12-30 Implementation of brew(), generateSteam(), dispenseHotWater(), standby() and corresponding variables. %TODO Add 6th state for generateSteam(), change checkControlButton(), add variable syncs for mqtt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
2020-12-31 Added checkBrewSwitches and state 6 steam. %TODO adding variable to sync via blynk and mqtt
2021-01-02 Added syncs for eeprom and blynk #TODO check mqtt libs for mqtt variable updates.
2021-01-05 add vscode filess to git for arduino
2021-01-09 deleted whitespace
2021-01-10 bug fixes
2021-01-11 debug
2021-01-11 test panel
2021-01-12 bugfix high heating power after steaming
2021-01-30 2.5.0 beta 1: internal test version
2021-01-30 - 2.6.0 beta 1: - !!ATTENTION: THIS VERSION IS NOT YET TESTED!! - !!ATTENTION: THIS VERSION IS NOT YET TESTED!! - !!ATTENTION: THIS VERSION IS NOT YET TESTED!! - Merged PR by finnito which changed/ex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
2021-01-31 - 2.6.0 beta 2: - !!ATTENTION: THIS VERSION IS NOT YET TESTED!! - !!ATTENTION: THIS VERSION IS NOT YET TESTED!! - !!ATTENTION: THIS VERSION IS NOT YET TESTED!! - Bugfix: DEBUG_FORCE_GPIO_CHECK workin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
2021-01-31 Fix Display Logo when steaming.
2021-02-03 - 2.6.0 beta 4: - New feature: Set userConfig.h ROTATE_DISPLAY to rotate display 180 degree. - New feature: BrewReadyLed (now called HardwareLed) configured with ENABLE_HARDWARE_LED also lights up wh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
2021-02-15 - 2.6.0 beta 5: - !!ATTENTION: THIS VERSION IS NOT FULLY TESTED!! - BREAKING CHANGE: OnlyPid=1: Software based brewDetection is set with "2" (and not "1"!) in userConfig BREWDETECTION. - Feature: Onl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
2021-02-17 - 2.6.0 beta 7: - Feature/Fix: New setting STEAM_READY_TEMP to show our special steaming-icon only when temperature is above. - There is support for special "in-steaming-state" icons, but I am in no 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
2021-02-18 - 2.6.0: - Merged PR by finnito which changed/extended: (MANY THANKS FINNITO) - Added support for ECM espresso maschine including logo. - Added/Extended support for special functions (steam, hotwater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
2021-02-19 remove trailing whitespaces here and there
2021-02-20 - 2.6.1: - Feature: Hardware-Led in addition to simple LEDs also support WS2812b LED (stripes) (MANY THANKS P1Rebo for the PR)
2021-03-09 - 2.7.0 beta 1: - Attention: Until now the ESP32 code was only simulated and not running on real-world maschines. - Feature: Support ESP32 with CPU pinning for improved performance. - Unfortuately th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
2021-03-10 Update userConfig.h.SAMPLE
    Example for a full HW controlled Toogle function.
2021-03-16 - 2.7.0 beta 3: - Feature: (ENABLE_HARDWARE_LED=2) New settings ENABLE_HARDWARE_LED_RGB_ON/ENABLE_HARDWARE_LED_RGB_OFF to set specific colors. - Fix: esp8266: Display is again working on first couple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
2021-03-17 Update rancilio-pid.ino
    fastLED change to colour name
2021-03-17 - 2.7.0 beta 4: - Fix: ENABLE_HARDWARE_LED_RGB_ON/OFF now working (Thanks Helge!) - minor stuff
2021-03-24 - 2.7.0 beta 5: - (ESP32) Added two new [circuit-diagrams](https://github.com/medlor/bleeding-edge-ranciliopid/tree/master/circuit-diagrams) which show the complete wiring in "full-control" upgrade. 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
2021-04-06 - 2.7.0: - Feature: FULLY SUPPORT ESP32 with CPU pinning for improved performance. - Unfortuately there is no mqtt-server broker library available for ESP32. (MQTT_ENABLE must not be 2 or disabled on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
2021-04-09 - 2.7.1: - Update ZACwire-Library to v1.3.1.
2021-04-15 - 2.7.1: - Added PR for automatic cleaning mode (Thanks to urbantrout/Harald). - Adaptions: - New cleaning icon: ["washing hand"](https://thenounproject.com/matfine/collection/cleaning-icon/?i=274970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
2021-04-16 - 2.7.1b: - Fix: DISPLAY_TEXT_STATE is not displayed when screensaver is running.
2021-04-22 ZACWire-test adapted
2021-04-22 Fix: BLynk SLEEPING=1 is also ignored on startup.
2021-04-25 Define actionController() in controls.h
2021-04-25 Gitignore userConfig.h*, ie to allow userConfig.h.bak or userConfig.h.2.6.1 backups
2021-05-14 - 2.8.0: - Feature: Add support to detect low water using a VL53L0X Time of Flight distance sensor. see [Howto](https://github.com/medlor/bleeding-edge-ranciliopid/wiki/Water-level-measurement-using-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
2021-06-04 - 2.9.0b1: - Not yet tested on live machine! - Add full support for platformio and fix compile warnings. - Force espressif8266 to Version 2 (until external libs are adapted) - Arduino IDE: Remove som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
2021-06-07 - 2.9.0b2: - Fix: controllerActions: Improve debouncing of analog(ADC) and digital buttons/switches. - Code cleanup and compiler warning fixes.
2021-06-09 - 2.9.0b3: - code indentation
2021-09-12 - 2.9.0b6: - Update ESP32 schematic to reflect recommendation to use 5v (instead of 3.3v) for the TSIC. - Fix: Temporary using custom "Zacwire for TSIC" due to a bug inducting partly wrong temperatur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
2021-09-13 Add missing DEBOUNCE_ flags.
2021-09-15 - 2.9.0b8: - Temperature outliner detection activated for a wider range of situations (this shall fix brew-detection) - Minor adaption to PID tuning.
2021-09-21 - 2.9.0b9: - Improve steaming cycle-times.
2021-09-24 Files with ending ``:com.dropbox.attrs`` prevent switching to that branch Delete Case upper_v1.stl:com.dropbox.attrs Delete Case upper_v5.stl:com.dropbox.attrs
2021-09-30 - 2.9.0b10: - Remove latest networt tunings (wifiSleep, keepalive, timeouts), because it looks like in some situations they break. - Changed userConfig.Sample.h recommended defaults
2021-10-28 - 2.9.0b12: - Recover temperature when maschine had hung during steaming. - Add logging when loop() is taking too much time.
2021-10-31 Added video section
2021-11-05 - 3.0.0: - Project is getting renamed to "Perfect Coffee PID". - Improve temperature readings to reduce undesireable actions of the PID controller: - Detect outliers near setpoint and fix them automa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
2021-11-08 - remove network tuning
2021-12-10 Add support for Thermistor K-type with MAX6675
2021-12-11 - 3.1.0_beta2: - Initial support for Thermistor K-type with MAX6675 (Thanks to aschoelzhorn!). - userConfig.h: - Added: TEMPSENSOR (default=2)
2021-12-22 3.1.0_beta3_test
2021-12-22 - 3.1.0_beta3: - Add support for up to 3 "Profiles", which can be used to quickly switch between different brew setings (eg. when different beans are used). - An individual profile comprises of follo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
2021-12-29 - 3.1.0_beta4: - test version for MAX6675K with additional debug information. - MAX6675K decreased refreshTempInterval from 260ms to 200ms.
2022-01-03 - 3.1.0_beta5: - latest test version for MAX6675K to mitigate issues due to inaccurate readings.
2022-01-25 Getting initial code together to support the HX711
2022-01-25 Updated brew() to do weight based brewing
2022-01-28 - 3.2.0 beta_2: - ALPHA! - Initial scale code is based on HX711_ADC by Olav Kallhovd (https://github.com/olkal/HX711_ADC) - scale functionality refactored: - Rewrite of brew() function to supports st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
2022-01-30 - 3.2.0 beta_3: - ALPHA! - Scale: - Add asyncTare to auto-tare cup weight while (pre-infusion) is running (it should be completed before the first drops add weight). - If auto tare at start of brew f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
2022-02-01 - 3.2.0 beta_5: - ALPHA! - Fix: Readded coldstart which I have disabled for testing. - Scale: - After brew is finished weight is measured fore an additional 2 seconds (to include dripping in the tota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
2022-02-02 - 3.2.0 beta_6: - ALPHA! - Scale: Fix missing getNewCalibration()
2022-02-08 remove submodule
2022-02-08 Add library/HX711_ADC_fix
2022-02-08 Increase version in Readme.md
2022-02-14 - 3.2.0 beta_8: - Setup guide in [Wiki](https://github.com/medlor/bleeding-edge-ranciliopid/wiki/Scale-Setup) - [3D Scale Case made by Hoodie](https://www.thingiverse.com/thing:5226789) (Many thanks 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
2022-03-02 Add pictures of the PCP scale
2022-08-25 add SH1106 in SPI, fix DISPLAY_HARDWARE config
2022-08-31 - 3.2.1 beta 2: - Feature: Add support for SH1106 in SPI mode. Thanks piontec! - Fix: SSD1306 support should also work again. Thanks piontec!
2022-09-27 allow user to configure I2C pins for OLED screen
2022-09-30 finsih splitting realy config
2022-09-30 - 3.2.1 beta 3: - Feature: Add support for custom display pins (see DISPLAY_I2C_SCL, DISPLAY_I2C_SDA). Thanks piontec! - userConfig.h Changes: - Added DISPLAY_I2C_SCL, DISPLAY_I2C_SDA (default 255).
2022-11-21 - 3.2.1: - Feature: Add support for SH1106 in SPI mode. Thanks piontec! - Feature: Add support for custom display pins (see DISPLAY_I2C_SCL, DISPLAY_I2C_SDA). Thanks piontec! - Feature: Distinguish t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
2022-11-23 define sensor mock as own sensor type
2022-11-23 moved blynk code into own files to reduce file size of rancilio-pid.ino ( ~300 lines of code)
2023-01-02 minor PR adaptions
2023-01-03 Add github runner
2023-01-03 adapt sample config to enable testing
2023-03-16 - 3.2.3 beta1: - Fix: Wifi stability improvements. - Disable WiFi Power Safe. - Reduce WiFi retry wait times. - WiFi instability by adding housekeeping times. - Fix: Support for Expressif v5.3. - Per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
2023-03-18 Syntax Problem
    Fixed Problem with referenz to file.
2023-03-18 - 3.2.3 beta2: - Fix: esp8266 compile issues. - Fix: Newly beta1 added esp8266 compile issues. - Fix: Blynk working again with latest version. - Fix: Some "include" issues when arduinoIDE is used. Th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
2023-03-27 - 3.2.3 beta3: - Changed minimum retry timer when mqtt/blynk disconnects happen from 160s to 60s. - Added Blynk state caching.
2023-03-31 Extract blocks of code to methods for better readability
2023-04-15 - 3.2.3 beta4: - Feature: Enable bigger status icons when ENABLE_BIG_STATUS_ICONS is set to 1 (default 0). Many thanks aschoelzhorn! - Refactor: Code refactoring. Many thanks aschoelzhorn! - Fix: Cha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
2023-05-01 - 3.2.3 beta5: - On OTA Update show special logo and progress. Thanks aschoelzhorn!
2023-05-05 * extracted and moved Wifi code to connection.cpp (maybe there is better name for it) * reorganized OTA (init and handle), OTA code still in "rancilio-pid.ino" because of timer stuff * separated decl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
2023-05-14 moved STATE_ defines to enum class
2023-05-15 - 3.2.3: - Feature: On OTA Update show special logo and progress. Thanks aschoelzhorn! - Feature: Enable bigger status icons when ENABLE_BIG_STATUS_ICONS is set to 1 (default 0). Many thanks aschoelz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
2023-05-17 - 3.2.4 beta 2: - minor refactorings.
2023-08-26 - 3.2.4: - Many more refactorings by aschoelzhorn. Thanks again! - Seperated wifi, temperature and other code to dedicated files. - Introduces rancilio-enums.h file and replaced some defines with enu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
2023-09-04 Add PicoMQTT broker

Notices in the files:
README.md:
- ["menu"](https://thenounproject.com/icon/menu-2943760/) by [Mat fine](https://thenounproject.com/matfine) from [the Noun Project](https://thenounproject.com/icon/tasks-2943947/) licensed under [CC BY 3.0](https://creativecommons.org/licenses/by/3.0/legalcode)
- ["Glückliche Gesichter Emoticons"](https://pixabay.com/de/illustrations/gl%C3%BCckliche-gesichter-emoticons-5049116/) by [Annalise Batista](https://pixabay.com/de/users/annaliseart-7089643/) licensed under [Pixabay license](https://pixabay.com/de/service/terms/#license)
